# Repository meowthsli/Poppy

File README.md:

Poppy
=====

Poppy Keyboard Backlight

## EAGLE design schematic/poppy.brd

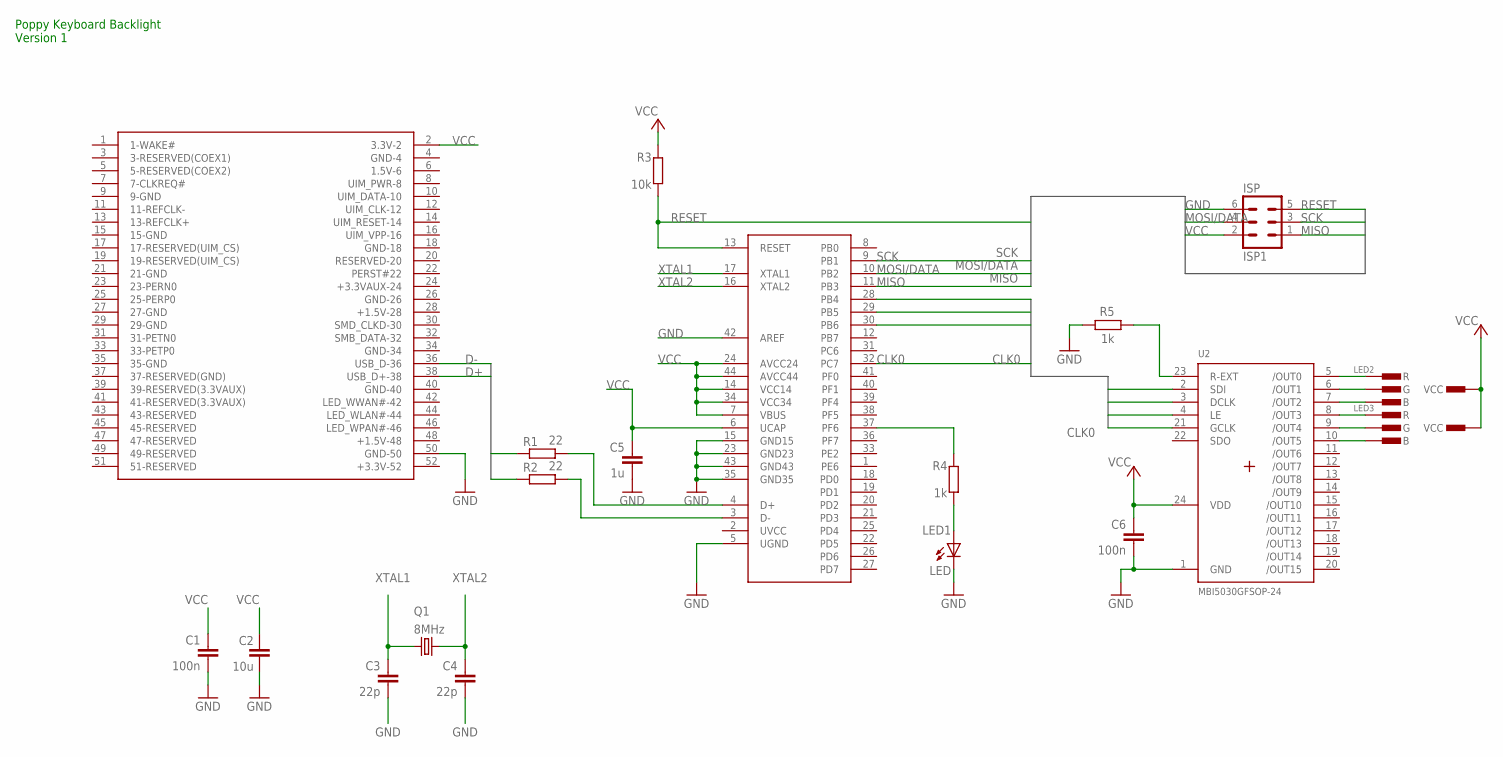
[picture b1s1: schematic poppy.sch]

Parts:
C1, C6: 100n; C1206K
C2: 10u; C1812
C3, C4: 22p; C1206K
C5: 1u; C1206K
EDGE: FULL-MINI-PCI-E
ISP: ISP1; MA03-2
LED1: LED; CHIPLED_0805
LED2, LED3: CON-RGB-LED-EXT; CON-RGB-LED-TH-EXT
Q1: 8MHz; CTS406
R1, R2: 22; R1206
R3: 10k; R1206
R4, R5: 1k; R1206
U1: ATMEGA16U4TQFP44; ATMEGA16U4_TQFP
U2: MBI5030GFSOP-24; _LEDDRIVERS_SOP24-300-1.00

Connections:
CLK0: U1.32 (PC7), U2.21 (GCLK)
D+: EDGE.38 (USB_D+-38), R1.2
D-: EDGE.36 (USB_D-36), R2.2
DCLK: U1.28 (PB4), U2.3 (DCLK)
GND: C1.2, C2.2, C3.2, C4.2, C5.2, C6.2, EDGE.50 (GND-50), EDGE.GND@1 (GND), EDGE.GND@2 (GND), ISP.6, LED1.C, R5.1, U1.5 (UGND), U1.15 (GND15), U1.23 (GND23), U1.35 (GND35), U1.42 (AREF), U1.43 (GND43), U2.1 (GND)
LATCH: U1.30 (PB6), U2.4 (LE)
MISO: ISP.1, U1.11 (PB3)
MOSI/DATA: ISP.4, U1.10 (PB2)
unnamed: R4.2, U1.37 (PF6)
unnamed: R5.2, U2.23 (R-EXT)
unnamed: LED2.3.R (R), U2.5 (/OUT0)
unnamed: LED2.2.G (G), U2.6 (/OUT1)
unnamed: LED2.1.B (B), U2.7 (/OUT2)
unnamed: LED1.A, R4.1
unnamed: R1.1, U1.4 (D+)
unnamed: R2.1, U1.3 (D-)
unnamed: LED3.3.R (R), U2.8 (/OUT3)
unnamed: LED3.2.G (G), U2.9 (/OUT4)
unnamed: LED3.1.B (B), U2.10 (/OUT5)
RESET: ISP.5, R3.1, U1.13 (RESET)
SCK: ISP.3, U1.9 (PB1)
SDI: U1.29 (PB5), U2.2 (SDI)
VCC: C1.1, C2.1, C5.1, C6.1, EDGE.2 (3.3V-2), ISP.2, LED2.4.VCC (VCC), LED3.4.VCC (VCC), R3.2, U1.6 (UCAP), U1.7 (VBUS), U1.14 (VCC14), U1.24 (AVCC24), U1.34 (VCC34), U1.44 (AVCC44), U2.24 (VDD)
XTAL1: C3.1, Q1.1, U1.17 (XTAL1)
XTAL2: C4.1, Q1.3 (2), U1.16 (XTAL2)

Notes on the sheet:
Poppy Keyboard Backlight Version 1

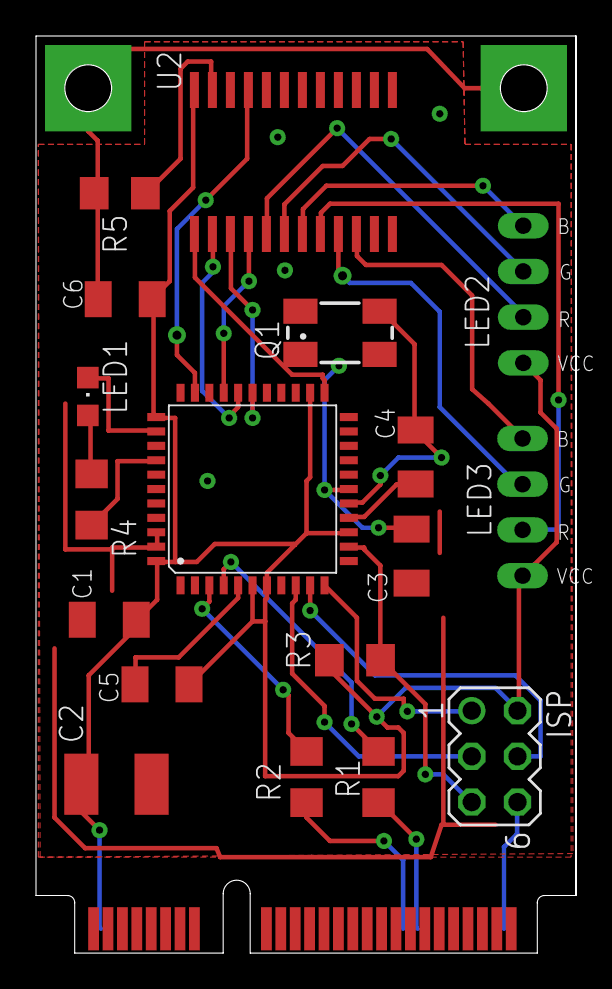
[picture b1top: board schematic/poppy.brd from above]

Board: 2 copper layers, 30.0 x 51.0 mm, 19 parts (0 on the bottom side), 25 nets.

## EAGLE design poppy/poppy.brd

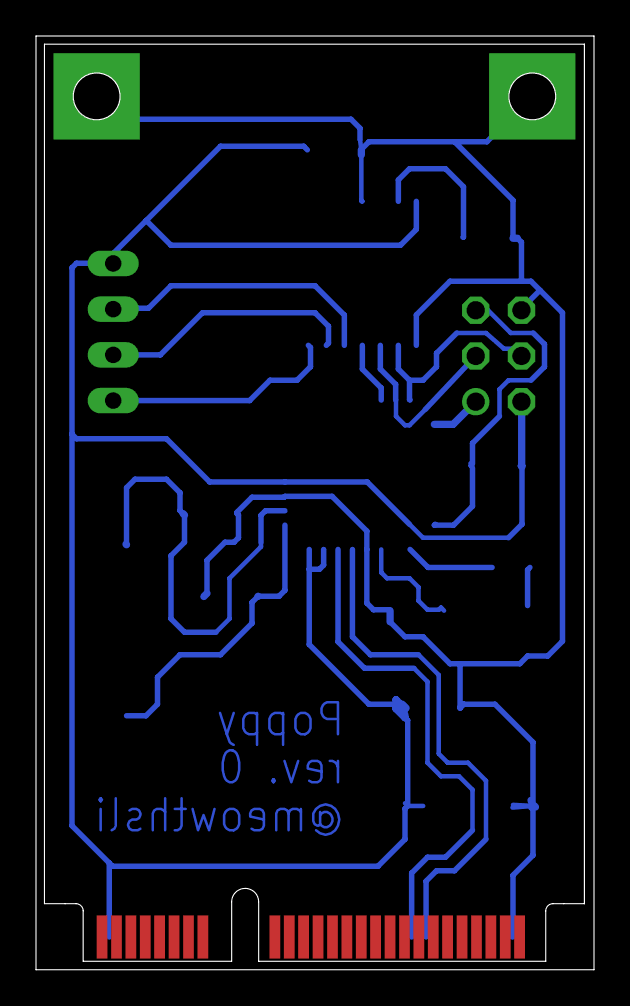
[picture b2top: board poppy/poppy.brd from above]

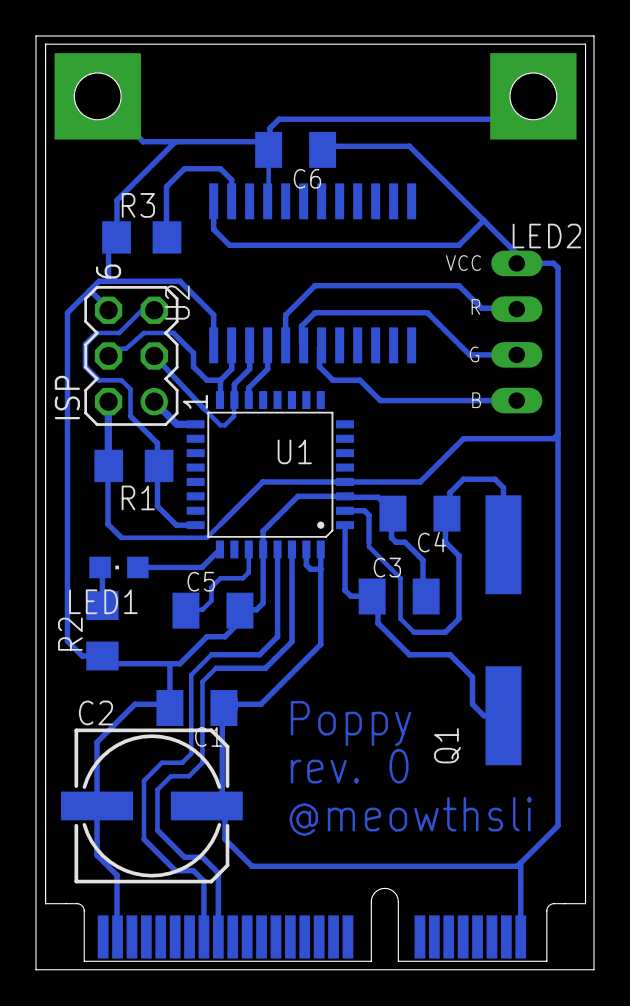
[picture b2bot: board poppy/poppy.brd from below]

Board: 2 copper layers, 31.0 x 51.9 mm, 16 parts (15 on the bottom side), 18 nets.

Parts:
C1, C6: 100n; C1206K
C2: 10u; 153CLV-0807
C3, C4: 22p; C1206K
C5: 1u; C1206K
EDGE: FULL-MINI-PCI-E
ISP: ISP1; MA03-2
LED1: LED; CHIPLED_0805
LED2: CON-RGB-LED-EXT; CON-RGB-LED-TH-EXT
Q1: 8MHz; CSM-7X-DU
R1: 10k; R3216
R2, R3: 1k; R3216
U1: ATUSB; VQFP32
U2: MBI5039; SOP24-300-1.00

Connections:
D+: EDGE.38, U1.29
D-: EDGE.36, U1.30
GND: C1.2, C2.-, C3.2, C4.2, C5.2, C6.2, EDGE.50, EDGE.GND@1, EDGE.GND@2, ISP.6, R2.1, R3.1, U1.3, U1.28, U2.1, U2.21
LATCH: U1.14, U2.4
MISO: ISP.1, U1.17
MOSI/DATA: ISP.4, U1.16, U2.2
unnamed: LED1.A, U1.25
unnamed: R3.2, U2.23
unnamed: LED2.3.R, U2.5
unnamed: C5.1, U1.27
unnamed: LED2.2.G, U2.6
unnamed: LED2.1.B, U2.7
unnamed: LED1.C, R2.2
RESET: ISP.5, R1.1, U1.24
SCK: ISP.3, U1.15, U2.3
VCC: C1.1, C2.+, C6.1, EDGE.2, ISP.2, LED2.4.VCC, R1.2, U1.4, U1.31, U1.32, U2.24
XTAL1: C3.1, Q1.1, U1.1
XTAL2: C4.1, Q1.2, U1.2

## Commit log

2013-01-21 Initial
2013-01-21 Refreshed to encoding
2013-01-23 Routed
2013-01-23 Routed 65%
2013-01-23 Ready to etch!
2013-01-23 Layout fixes, testing
2013-01-23 Удалил временные файлы
2013-01-29 Ready to solder
2013-01-29 Rerouted more carefully
2013-01-29 Added printed objects
2013-03-01 rearranged working dir
2013-03-01 atmega16u4 tqfp44 added
2013-03-02 routed everything
2013-03-02 rerouted some parts
2013-03-02 printed
2013-03-02 fixed usb diff line
2013-03-05 added miniusb and second led
2013-03-06 png from board-2
2013-03-06 reroute
2013-03-26 first production
2013-03-26 prod is ready
2013-03-26 prod is ready 2 lol
2013-03-27 added border layer
